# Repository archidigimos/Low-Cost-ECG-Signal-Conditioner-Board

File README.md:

# Low-Cost-ECG-Signal-Conditioner-Board
Analog Front End and Digital Back End PCB for ECG signal conditioning.

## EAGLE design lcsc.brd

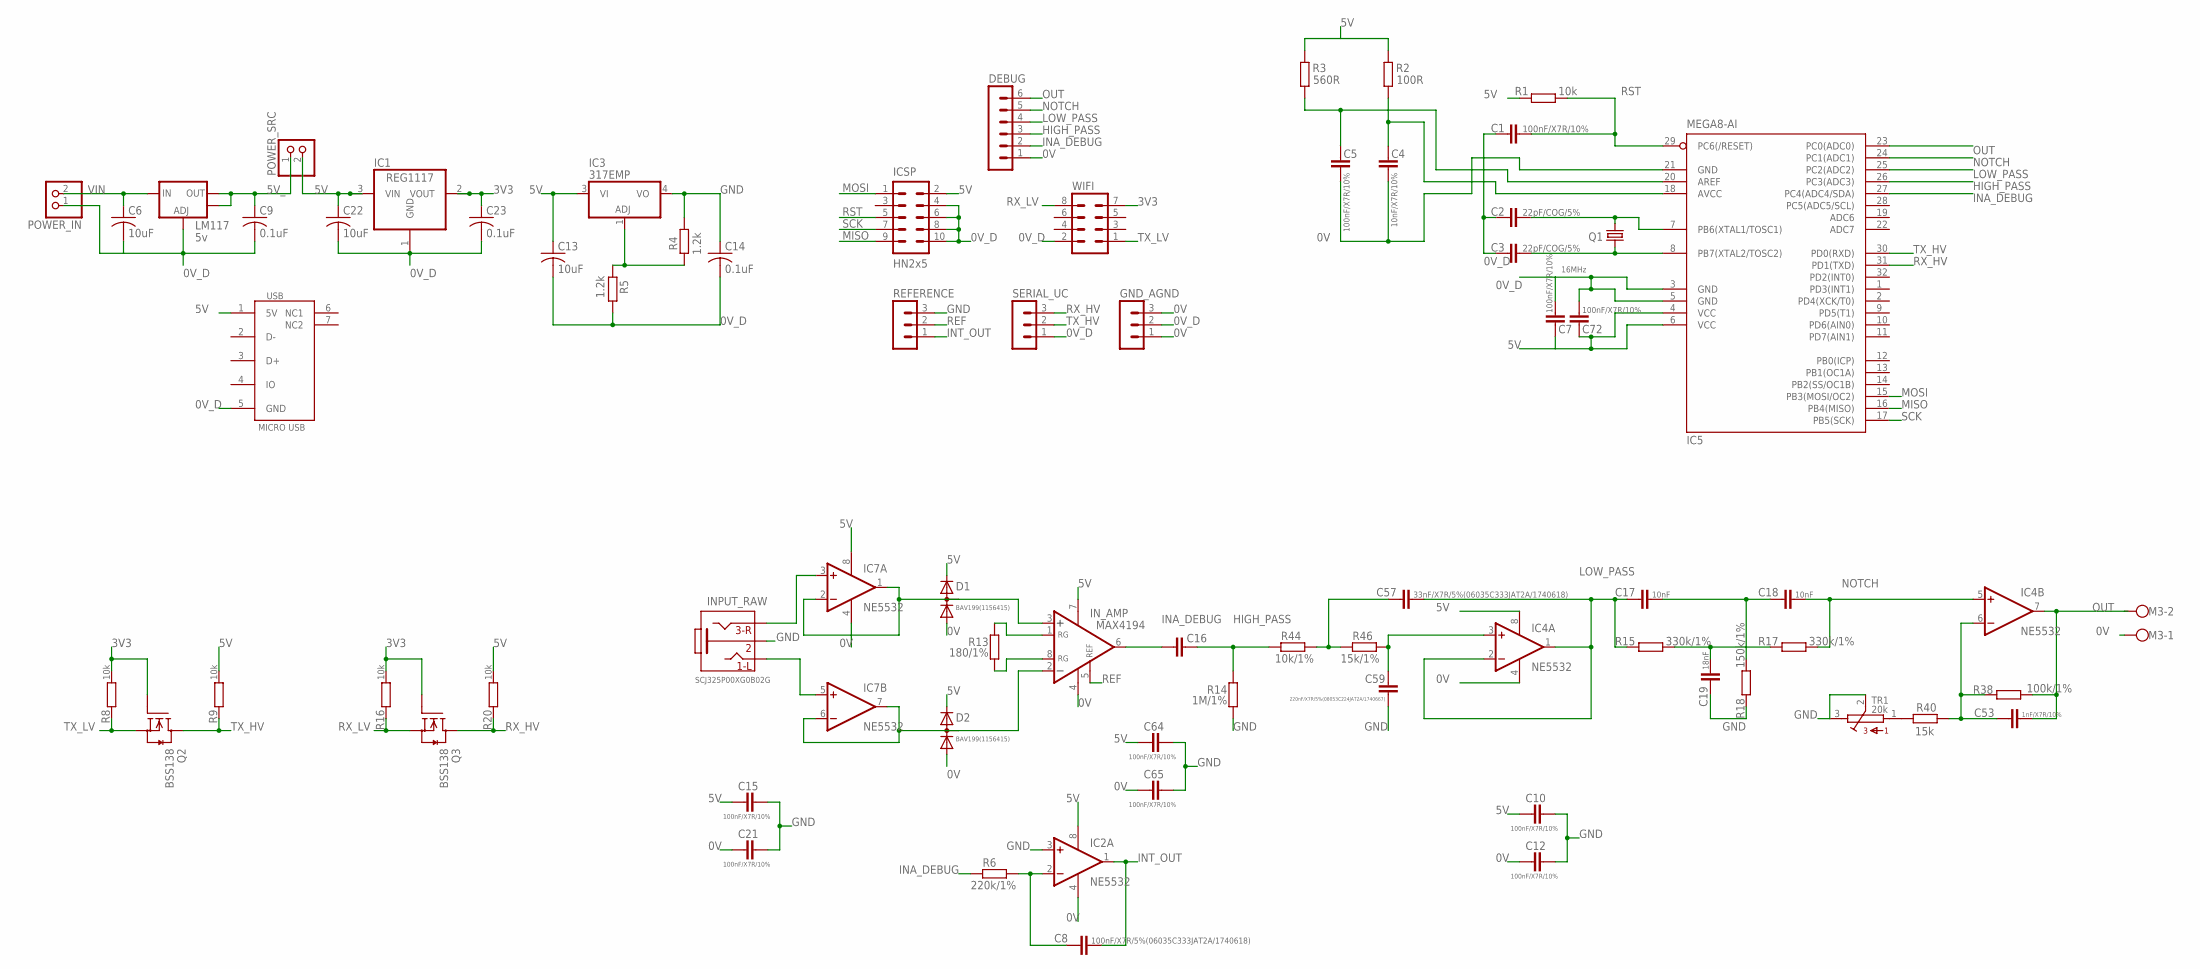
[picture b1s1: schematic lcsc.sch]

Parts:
C1, C5, C7, C10, C12, C15, C21, C64, C65, C72: 100nF/X7R/10%; C0603_DWS
C2, C3: 22pF/COG/5%; C0603_DWS
C4: 10nF/X7R/10%; C0603_DWS
C6, C13, C22: 10uF; C0805
C8: 100nF/X7R/5%(06035C333JAT2A/1740618); C0603_DWS
C9, C14, C23: 0.1uF; C0805
C16: 1uF/X5R/10%; C0603_DWS
C17, C18: 10nF; C0603_DWS
C19: 18nF; C0603_DWS
C53: 1nF/X7R/10%; C0603_DWS
C57: 33nF/X7R/5%(06035C333JAT2A/1740618); C0603_DWS
C59: 220nF/X7R/5%(08053C224JAT2A/1740667); C0805_5MIL_DWS
D1, D2: BAV199(1156415); SOT23C(BAT54S)
DEBUG: MA06-1
GND_AGND: MA03-1
IC1: REG1117; SOT223
IC2, IC4, IC7: NE5532; SO08
IC3: 317EMP; SOT223
IC5: MEGA8-AI; TQFP32-08
ICSP: HN2x5; ML10_NEW
INPUT_RAW: SCJ325P00XG0B02G; PHONE_JACK-SMD
IN_AMP: MAX4194; SOIC8
LM117: 5v; SOT223
M3: W237-102
POWER_IN: PINHD-1X2; 1X02
POWER_SRC: PINHD-1X2; 1X02
Q1: 16MHz; HC49/SMD2_THIN
Q2, Q3: BSS138; SOT23
R1, R8, R9, R16, R20: 10k; R0603_5MIL_DWS
R2: 100R; R0603_5MIL_DWS
R3: 560R; R0603_5MIL_DWS
R4, R5: 1.2k; R0603_5MIL_DWS
R6: 220k/1%; R0603_5MIL_DWS
R13: 180/1%; R0603_5MIL_DWS
R14: 1M/1%; R0603_5MIL_DWS
R15, R17: 330k/1%; R0603_5MIL_DWS
R18: 150k/1%; R0603_5MIL_DWS
R38: 100k/1%; R0603_5MIL_DWS
R40: 15k; R0603_5MIL_DWS
R44: 10k/1%; R0603_5MIL_DWS
R46: 15k/1%; R0603_5MIL_DWS
REFERENCE: MA03-1
SERIAL_UC: MA03-1
TR1: 20k; S64Y
USB: MICRO_USB
WIFI: MA04-2

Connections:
0V: C4.2, C5.2, C12.1, C21.1, C65.1, D1.1 (A), D2.1 (A), DEBUG.1, GND_AGND.1, GND_AGND.3, IC2.4 (V-), IC4.4 (V-), IC5.21 (GND), IC7.4 (V-), IN_AMP.4 (V-), M3.1
0V_D: C1.2, C2.2, C3.2, C6.2, C7.2, C9.2, C13.2, C14.2, C22.2, C23.2, C72.2, GND_AGND.2, IC1.1 (GND), IC5.3 (GND), IC5.5 (GND), ICSP.4, ICSP.6, ICSP.8, ICSP.10, LM117.1 (ADJ), POWER_IN.1, R5.1, SERIAL_UC.1, USB.5 (GND), WIFI.2
3V3: C23.1, IC1.2 (VOUT), Q2.1 (G), Q3.1 (G), R8.2, R16.2, WIFI.7
4V_REF_ADC: C5.1, IC5.20 (AREF), R3.1
5V: C7.1, C10.1, C13.1, C15.1, C22.1, C64.1, C72.1, D1.2 (K), D2.2 (K), IC1.3 (VIN), IC2.8 (V+), IC3.3 (VI), IC4.8 (V+), IC5.4 (VCC), IC5.6 (VCC), IC7.8 (V+), ICSP.2, IN_AMP.7 (V+), POWER_SRC.2, R1.1, R2.2, R3.2, R9.2, R20.2, USB.1 (5V)
5V_: C9.1, LM117.2 (OUT), LM117.4 (OUT), POWER_SRC.1
GND: C10.2, C12.2, C14.1, C15.2, C19.1, C21.2, C59.2, C64.2, C65.2, IC2.3 (+IN), IC3.4 (VO), INPUT_RAW.1 (2), R4.1, R14.2, R18.1, REFERENCE.3, TR1.2, TR1.3
HIGH_PASS: C16.2, DEBUG.3, IC5.26 (PC3(ADC3)), R14.1, R44.1
INA_DEBUG: C16.1, DEBUG.2, IC5.27 (PC4(ADC4/SDA)), IN_AMP.6 (OUT), R6.1
INT_OUT: C8.2, IC2.1 (OUT), REFERENCE.1
LOW_PASS: C17.1, C57.2, DEBUG.4, IC4.1 (OUT), IC4.2 (-IN), IC5.25 (PC2(ADC2)), R15.1
MISO: IC5.16 (PB4(MISO)), ICSP.9
MOSI: IC5.15 (PB3(MOSI/OC2)), ICSP.1
unnamed: IN_AMP.1 (RG), R13.1
unnamed: IN_AMP.8 (RG), R13.2
unnamed: D1.3 (AK), IC7.1 (OUT), IC7.2 (-IN), IN_AMP.3 (+IN)
unnamed: IC7.3 (+IN), INPUT_RAW.2 (3)
unnamed: IC7.5 (+IN), INPUT_RAW.5 (1)
unnamed: IC3.1 (ADJ), R4.2, R5.2
unnamed: C8.1, IC2.2 (-IN), R6.2
unnamed: C19.2, R15.2, R17.1
unnamed: C17.2, C18.1, R18.2
unnamed: D2.3 (AK), IC7.6 (-IN), IC7.7 (OUT), IN_AMP.2 (-IN)
unnamed: C4.1, IC5.18 (AVCC), R2.1
unnamed: C3.1, IC5.8 (PB7(XTAL2/TOSC2)), Q1.2
unnamed: C2.1, IC5.7 (PB6(XTAL1/TOSC1)), Q1.1
unnamed: R40.2, TR1.1
unnamed: C53.1, IC4.6 (-IN), R38.1, R40.1
unnamed: C59.1, IC4.3 (+IN), R46.2
unnamed: C57.1, R44.2, R46.1
NOTCH: C18.2, DEBUG.5, IC4.5 (+IN), IC5.24 (PC1(ADC1)), R17.2
OUT: C53.2, DEBUG.6, IC4.7 (OUT), IC5.23 (PC0(ADC0)), M3.2, R38.2
REF: IN_AMP.5 (REF), REFERENCE.2
RST: C1.1, IC5.29 (PC6(/RESET)), ICSP.5, R1.2
RX_HV: IC5.31 (PD1(TXD)), Q3.3 (D), R20.1, SERIAL_UC.3
RX_LV: Q3.2 (S), R16.1, WIFI.8
SCK: IC5.17 (PB5(SCK)), ICSP.7
TX_HV: IC5.30 (PD0(RXD)), Q2.3 (D), R9.1, SERIAL_UC.2
TX_LV: Q2.2 (S), R8.1, WIFI.1
VIN: C6.1, LM117.3 (IN), POWER_IN.2

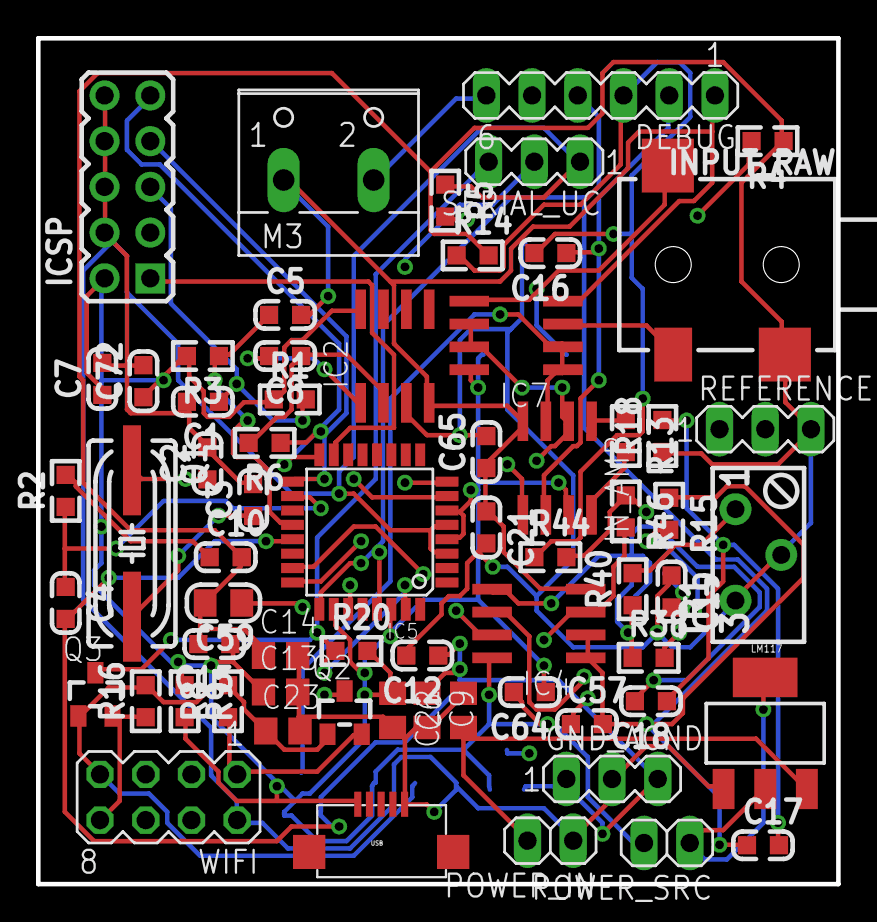
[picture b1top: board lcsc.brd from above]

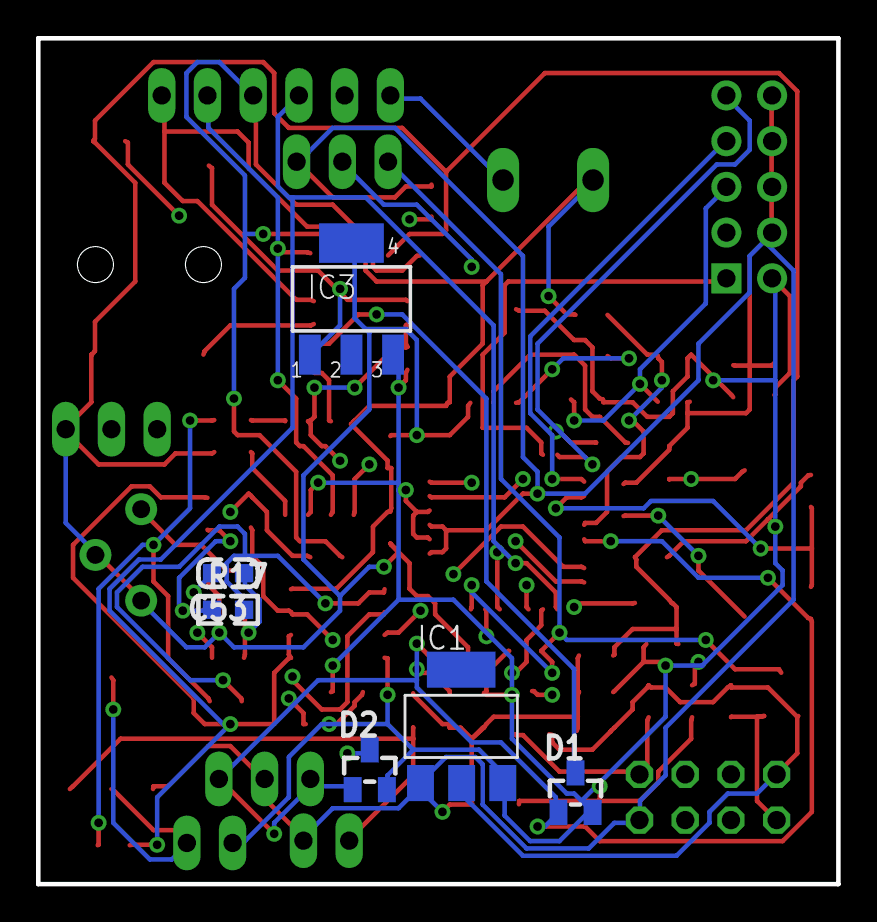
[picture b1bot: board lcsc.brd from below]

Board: 4 copper layers, 44.5 x 47.0 mm, 71 parts (6 on the bottom side), 40 nets.

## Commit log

2017-08-08 :boom::camel: Added .gitattributes & .gitignore files
2017-08-08 Screenshot

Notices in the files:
parts and their libraries:
m-pad-2.1: License : GNU General Public License version 2 (see bottom)
